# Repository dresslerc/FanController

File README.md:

FanController - Ceiling Fan Controller 
=========================================

Summary:
This project contains everything you need in order to control your Ceiling Fans from your smart phone.  We do this by tapping into the orginal RF remote of your fan by using Optocouplers. 

There are 3 key components to this project (1 Custom PCB Board, 2 Spark Core Code, and 3 Android/Android Wear app)

The PCB Board can be manufactured at OSHPark (https://oshpark.com/) for about 15$ with a 1-2 week turn around.  In the 'Docs' folder you will find a BOM that contains everything you need to build the board.

The controller for the circuit board is a Spark Core (http://spark.io).  The code is in 'Spark' folder.

You can find the oringal post for this project on https://community.spark.io/t/ceiling-fan-controller/6170

A video of the Android App: https://www.youtube.com/watch?v=2CFPBg5slgM

Android Weaer App: https://www.youtube.com/watch?v=zdxXlhGC8Go

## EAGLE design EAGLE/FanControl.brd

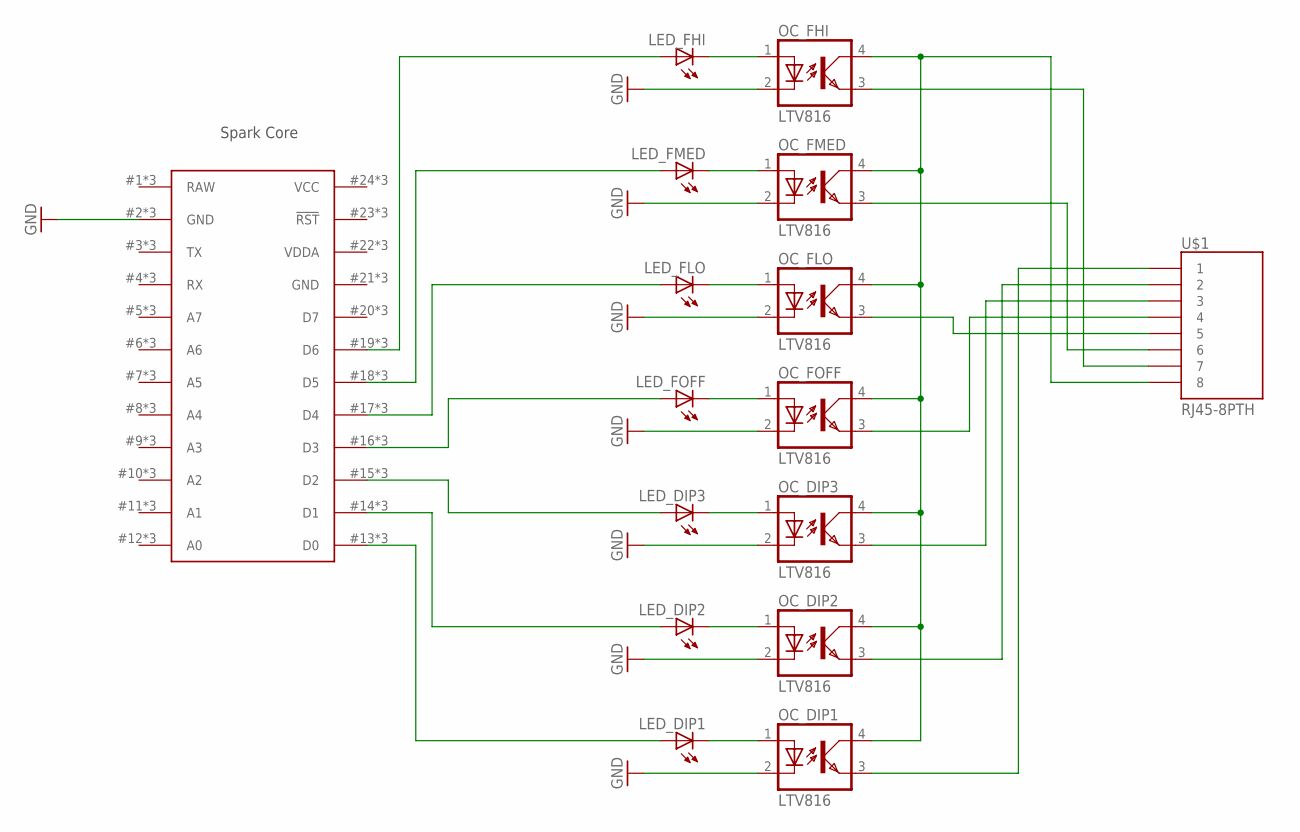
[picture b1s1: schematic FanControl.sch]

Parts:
LED_DIP1, LED_DIP2, LED_DIP3: LED3MM
LED_FHI: LED3MM
LED_FLO: LED3MM
LED_FMED: LED3MM
LED_FOFF: LED3MM
OC_DIP1, OC_DIP2, OC_DIP3: LTV816; DIL04
OC_FHI: LTV816; DIL04
OC_FLO: LTV816; DIL04
OC_FMED: LTV816; DIL04
OC_FOFF: LTV816; DIL04
U$1: RJ45-8PTH; RJ45-8
U$2: SPARK_CORE; SPARK_CORE_STACKABLE

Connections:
GND: OC_DIP1.2 (C), OC_DIP2.2 (C), OC_DIP3.2 (C), OC_FHI.2 (C), OC_FLO.2 (C), OC_FMED.2 (C), OC_FOFF.2 (C), U$2.2 (GND), U$2.21 (GND), U$2.#2 (GND), U$2.#21 (GND), U$2.@2 (GND), U$2.@21 (GND)
unnamed: OC_DIP1.4 (COL), OC_DIP2.4 (COL), OC_DIP3.4 (COL), OC_FHI.4 (COL), OC_FLO.4 (COL), OC_FMED.4 (COL), OC_FOFF.4 (COL), U$1.8
unnamed: OC_DIP1.3 (EMIT), U$1.1
unnamed: OC_DIP2.3 (EMIT), U$1.2
unnamed: OC_DIP3.3 (EMIT), U$1.3
unnamed: OC_FOFF.3 (EMIT), U$1.4
unnamed: OC_FLO.3 (EMIT), U$1.5
unnamed: OC_FMED.3 (EMIT), U$1.6
unnamed: OC_FHI.3 (EMIT), U$1.7
unnamed: LED_FHI.K (C), OC_FHI.1 (A)
unnamed: LED_FMED.K (C), OC_FMED.1 (A)
unnamed: LED_FLO.K (C), OC_FLO.1 (A)
unnamed: LED_FOFF.K (C), OC_FOFF.1 (A)
unnamed: LED_DIP3.K (C), OC_DIP3.1 (A)
unnamed: LED_DIP2.K (C), OC_DIP2.1 (A)
unnamed: LED_DIP1.K (C), OC_DIP1.1 (A)
unnamed: LED_DIP1.A, U$2.13 (D0), U$2.#13 (D0), U$2.@13 (D0)
unnamed: LED_DIP2.A, U$2.14 (D1), U$2.#14 (D1), U$2.@14 (D1)
unnamed: LED_DIP3.A, U$2.15 (D2), U$2.#15 (D2), U$2.@15 (D2)
unnamed: LED_FOFF.A, U$2.16 (D3), U$2.#16 (D3), U$2.@16 (D3)
unnamed: LED_FLO.A, U$2.17 (D4), U$2.#17 (D4), U$2.@17 (D4)
unnamed: LED_FMED.A, U$2.18 (D5), U$2.#18 (D5), U$2.@18 (D5)
unnamed: LED_FHI.A, U$2.19 (D6), U$2.#19 (D6), U$2.@19 (D6)
RAW: U$2.1 (RAW), U$2.#1 (RAW), U$2.@1 (RAW)
VCC: U$2.24 (VCC), U$2.#24 (VCC), U$2.@24 (VCC)
VDDA: U$2.22 (VDDA), U$2.#22 (VDDA), U$2.@22 (VDDA)

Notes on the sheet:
Spark Core

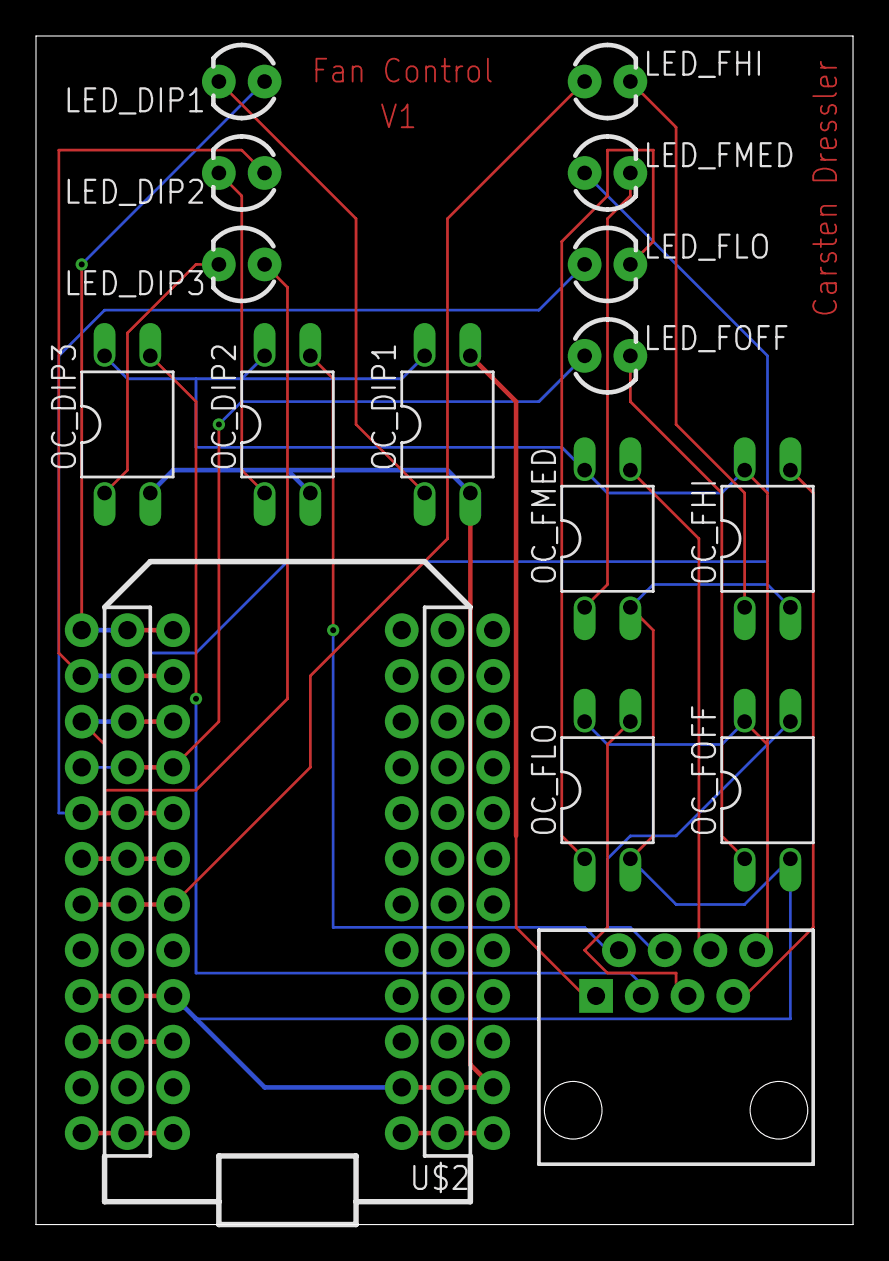
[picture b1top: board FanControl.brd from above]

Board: 2 copper layers, 45.4 x 66.0 mm, 16 parts (0 on the bottom side), 26 nets.

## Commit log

2014-09-10 :octocat: Added .gitattributes & .gitignore files
2014-09-10 Initial Commit
    Initial Release (Android Client, PCB Board, Spark Core App)
2014-09-10 Formatting update
    Formatting was incorrect from initial commit
2014-09-10 Formatting Fix
    Formatting issues from initial commit.
2014-09-10 Initial read.md

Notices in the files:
parts and their libraries:
SparkFun-Connectors: Licensing: CC v3.0 Share-Alike You are welcome to use this library for commercial purposes.
